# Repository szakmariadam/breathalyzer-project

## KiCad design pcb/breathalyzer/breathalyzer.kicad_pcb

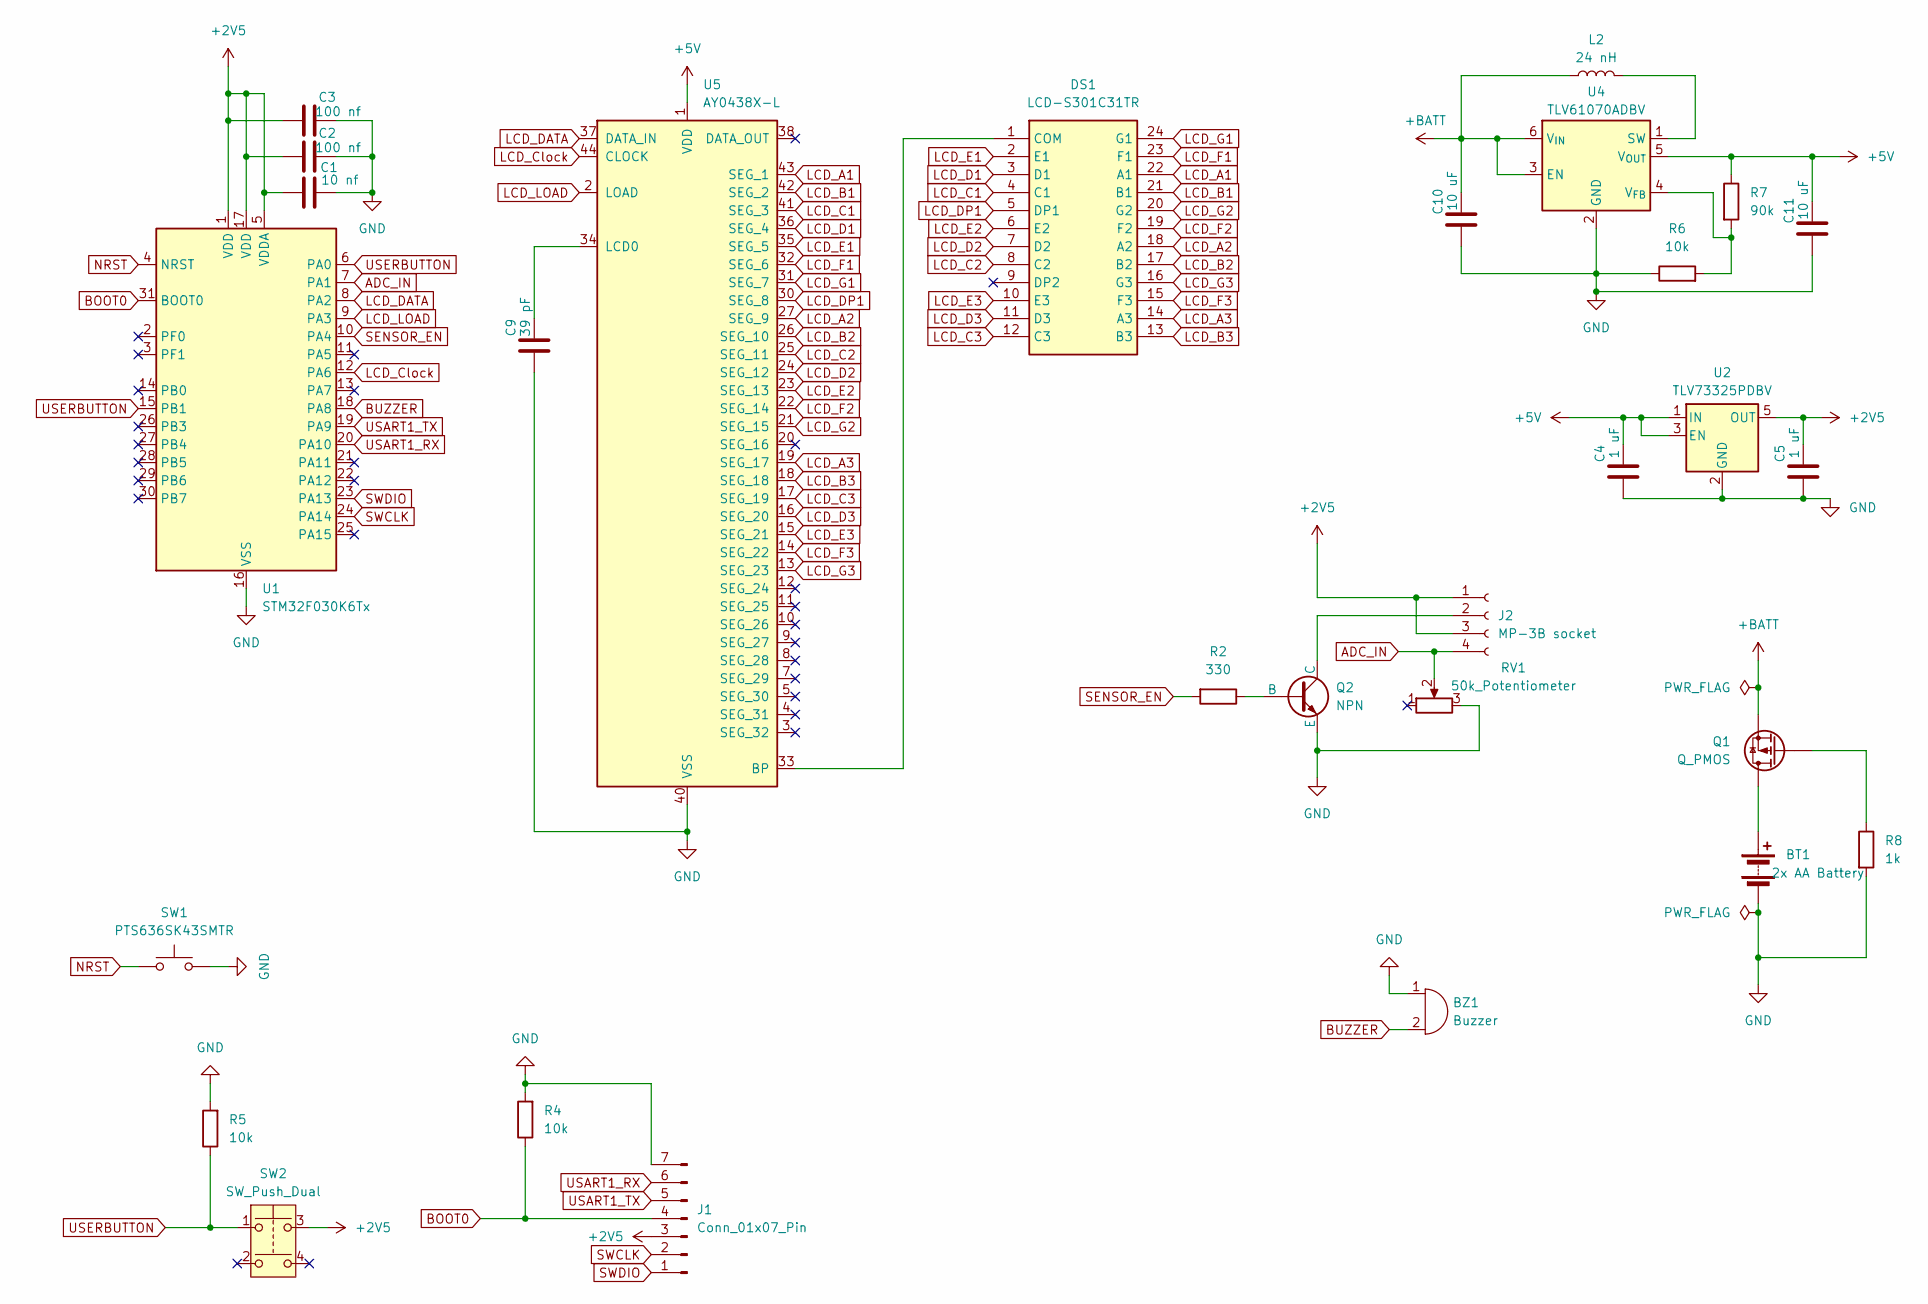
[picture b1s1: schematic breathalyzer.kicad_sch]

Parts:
BT1: 2x AA Battery; SHDRRA2W50P0X200_1X2_600X770X525P
BZ1: Buzzer; CPT1414680T
C1: 10 nf; C_01005_0402Metric
C2, C3: 100 nf; C_0402_1005Metric
C4, C5: 1 uF; C_0603_1608Metric
C9: 39 pF; C_0603_1608Metric
C10, C11: 10 uF; C_0805_2012Metric
DS1: LCD-S301C31TR; Mouser Part Number 696-LCD-S301C31TR
J1: Conn_01x07_Pin; HDRRA7W66P0X254_1X7_1778X229X274P
J2: MP-3B socket; 25SHB04TS
L2: 24 nH; L_1008_2520Metric
Q1: Q_PMOS; SOT-23-3
Q2: NPN; SOT-23-3
R2: 330; R_0805_2012Metric
R4, R5, R6: 10k; R_0603_1608Metric
R7: 90k; R_1206_3216Metric
R8: 1k; R_0603_1608Metric
RV1: 50k_Potentiometer; Potentiometer_ACP_CA9-H5_Horizontal
SW1: PTS636SK43SMTR; PTS636SM43JSMTRLFS
SW2: SW_Push_Dual; 430162085826
U1: STM32F030K6Tx; LQFP-32_7x7mm_P0.8mm
U2: TLV73325PDBV; SOT-23-5
U4: TLV61070ADBV; SOT-23-6
U5: AY0438X-L; PLCC-44

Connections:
+2V5: C1.1, C2.1, C3.1, C5.2, J1.3, J2.1, J2.3, SW2.3, U1.1 (VDD), U1.5 (VDDA), U1.17 (VDD), U2.5 (OUT)
+5V: C4.2, C11.2, R7.1, U2.1 (IN), U2.3 (EN), U4.5 (V_{OUT}), U5.1 (VDD)
+BATT: C10.2, L2.1, Q1.2 (S), U4.3 (EN), U4.6 (V_{IN})
ADC_IN: J2.4, RV1.2, U1.7 (PA1)
BOOT0: J1.4, R4.1, U1.31 (BOOT0)
BUZZER: BZ1.2 (-), U1.18 (PA8)
GND: BT1.2 (-), BZ1.1 (+), C1.2, C2.2, C3.2, C4.1, C5.1, C9.1, C10.1, C11.1, J1.7, Q2.3 (E), R4.2, R5.2, R6.1, R8.2, RV1.3, SW1.2, U1.16 (VSS), U1.32 (VSS), U2.2 (GND), U4.2 (GND), U5.40 (VSS)
LCD_A1: DS1.22 (A1), U5.43 (SEG_1)
LCD_A2: DS1.18 (A2), U5.27 (SEG_9)
LCD_A3: DS1.14 (A3), U5.19 (SEG_17)
LCD_B1: DS1.21 (B1), U5.42 (SEG_2)
LCD_B2: DS1.17 (B2), U5.26 (SEG_10)
LCD_B3: DS1.13 (B3), U5.18 (SEG_18)
LCD_C1: DS1.4 (C1), U5.41 (SEG_3)
LCD_C2: DS1.8 (C2), U5.25 (SEG_11)
LCD_C3: DS1.12 (C3), U5.17 (SEG_19)
LCD_Clock: U1.12 (PA6), U5.44 (CLOCK)
LCD_D1: DS1.3 (D1), U5.36 (SEG_4)
LCD_D2: DS1.7 (D2), U5.24 (SEG_12)
LCD_D3: DS1.11 (D3), U5.16 (SEG_20)
LCD_DATA: U1.8 (PA2), U5.37 (DATA_IN)
LCD_DP1: DS1.5 (DP1), U5.30 (SEG_8)
LCD_E1: DS1.2 (E1), U5.35 (SEG_5)
LCD_E2: DS1.6 (E2), U5.23 (SEG_13)
LCD_E3: DS1.10 (E3), U5.15 (SEG_21)
LCD_F1: DS1.23 (F1), U5.32 (SEG_6)
LCD_F2: DS1.19 (F2), U5.22 (SEG_14)
LCD_F3: DS1.15 (F3), U5.14 (SEG_22)
LCD_G1: DS1.24 (G1), U5.31 (SEG_7)
LCD_G2: DS1.20 (G2), U5.21 (SEG_15)
LCD_G3: DS1.16 (G3), U5.13 (SEG_23)
LCD_LOAD: U1.9 (PA3), U5.2 (LOAD)
NRST: SW1.1, U1.4 (NRST)
unnamed: BT1.1 (+), Q1.3 (D)
unnamed: DS1.1 (COM), U5.33 (BP)
unnamed: J2.2, Q2.1 (C)
unnamed: Q1.1 (G), R8.1
unnamed: Q2.2 (B), R2.1
unnamed: L2.2, U4.1 (SW)
unnamed: R6.2, R7.2, U4.4 (V_{FB})
unnamed: C9.2, U5.34 (LCD0)
SENSOR_EN: R2.2, U1.10 (PA4)
SWCLK: J1.2, U1.24 (PA14)
SWDIO: J1.1, U1.23 (PA13)
USART1_RX: J1.6, U1.20 (PA10)
USART1_TX: J1.5, U1.19 (PA9)
USERBUTTON: R5.1, SW2.1, U1.6 (PA0), U1.15 (PB1)

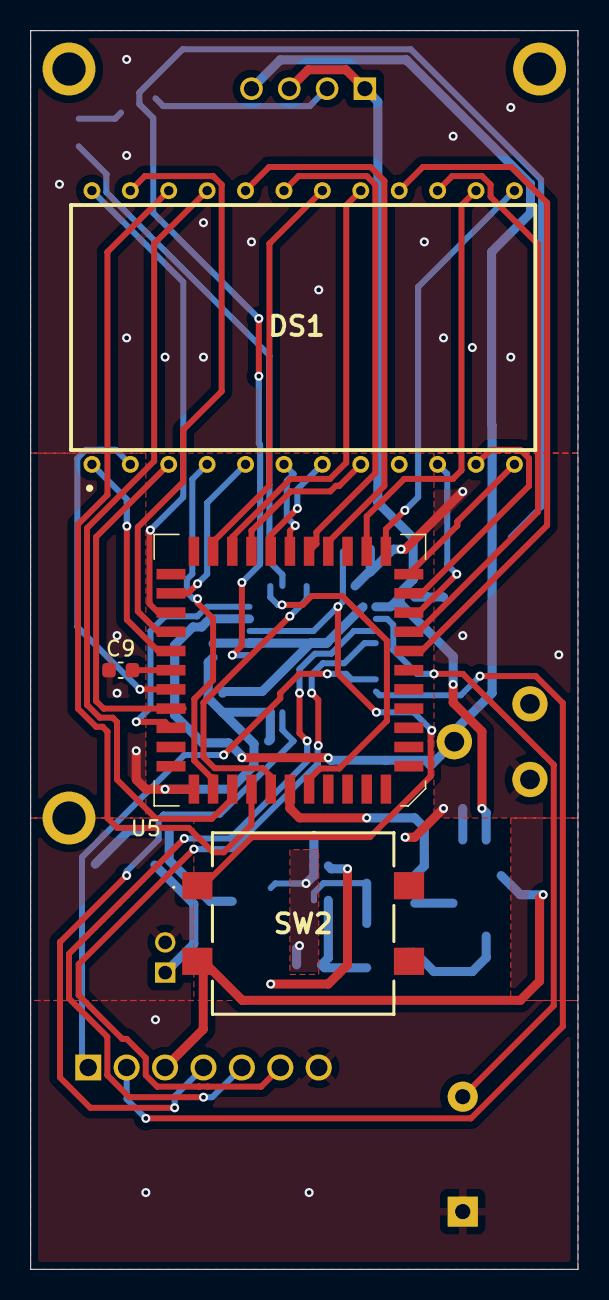
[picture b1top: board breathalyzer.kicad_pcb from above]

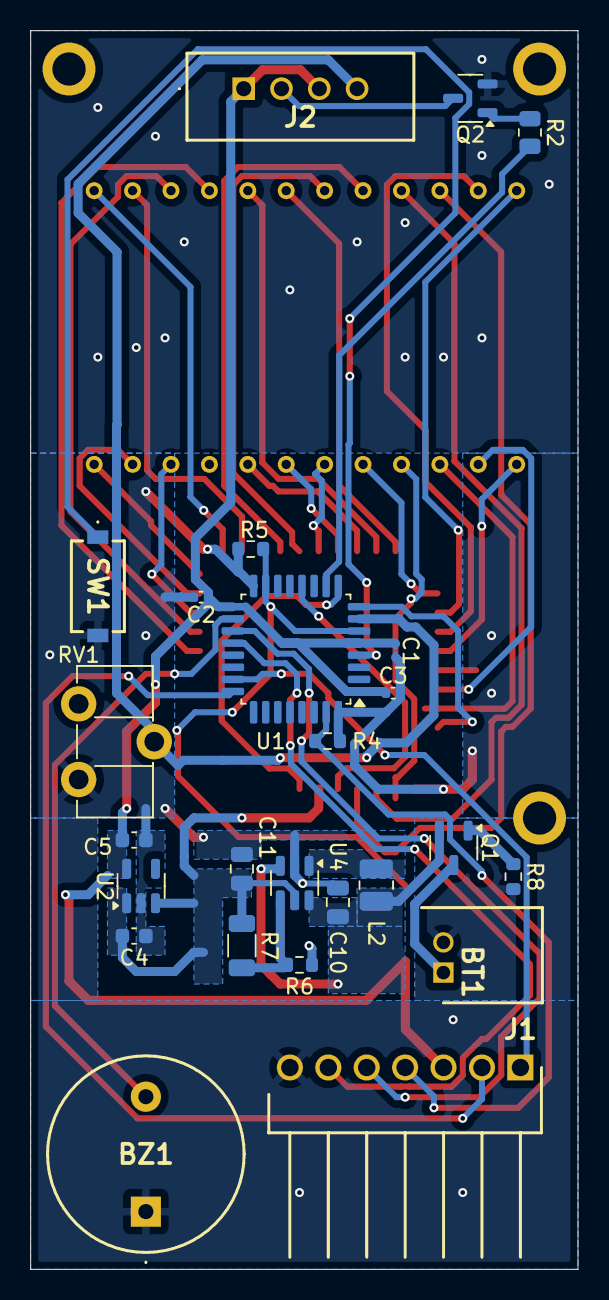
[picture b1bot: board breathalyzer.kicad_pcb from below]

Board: 2 copper layers, 36.2 x 81.9 mm, 32 parts (25 on the bottom side), 47 nets.

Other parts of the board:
H1, H1#2, H1#3: MountingHole; MountingHole_2.2mm_M2_ISO7380_Pad

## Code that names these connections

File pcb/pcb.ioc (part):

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Mcu.Name=STM32F030K6Tx
Mcu.Package=LQFP32
Mcu.UserName=STM32F030K6Tx
PA0.Mode=SYS_WakeUp0
PA0.Signal=SYS_WKUP1
PA1.Mode=IN1
PA1.Signal=ADC_IN1
PA10.Mode=Asynchronous
PA10.Signal=USART1_RX
PA13.Mode=Serial_Wire
PA13.Signal=SYS_SWDIO
PA14.Mode=Serial_Wire
PA14.Signal=SYS_SWCLK
PA2.Signal=GPIO_Output
PA3.Signal=GPIO_Output
PA4.GPIOParameters=PinState,GPIO_ModeDefaultOutputPP
PA4.GPIO_ModeDefaultOutputPP=GPIO_MODE_OUTPUT_PP
PA4.PinState=GPIO_PIN_RESET
PA4.Signal=GPIO_Output
PA6.Signal=S_TIM3_CH1
PA8.Signal=S_TIM1_CH1
PA9.Mode=Asynchronous
PA9.Signal=USART1_TX
PB1.Signal=GPXTI1
board=custom

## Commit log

2025-02-23 Empty project with LED blink
2025-02-23 GPIO8 for testing
2025-03-15 init GPIOs for 7 segment driver
2025-03-15 7 segment driver GPIOs testing
2025-03-16 Init ADC1
2025-03-19 project update
2025-03-19 polling ADC
2025-03-20 ADC calib
2025-03-20 PWM init
    Added HAL_ADC_Stop()
2025-03-26 ADC result averages
2025-03-27 PWM set to 2V31
2025-03-29 PWM set to 2V475
2025-03-30 project converted to CMake
2025-03-30 Imported project to vscode
2025-03-30 updated gitignore
2025-03-30 deleted ignored folders
2025-03-30 added back vscode config
2025-03-30 Enabled liveWatch in vscode
2025-03-30 setSegment function
2025-03-30 tim3 interrupt setup
    setSegment error handling
2025-03-31 Set up GPIOs to select digit
2025-04-02 7 segment driver
2025-04-02 7 segment driver fix
    display driver doesn't display empty digits
2025-04-02 set up user button
2025-04-02 ADC moved to PA1
    and sysWakeup was initialized on pa0
2025-04-03 callback function for TIM2
2025-04-03 10 sec timeout to standby
    init TIM4
    standby in interrupt
    wake up signal
2025-04-03 60 sec timeout to standby
2025-04-09 replaced blink with static power LED
    tim2 unused
2025-04-10 setup TIM2 as 1kHz 50D PWM for buzzer
    half sec beep on start
    commented standby timeout for dev
2025-04-14 UserButton GPIO changed
2025-04-14 added interrupt for UserButton
2025-04-15 removed the 1000 digit
    added fix decimal point
2025-04-15 7 segment displays 4.2f
2025-04-22 getADCvalue function
2025-04-22 sensor warmup function
2025-04-22 empty measure function on button press
2025-04-23 stop stby timeout while measuring
2025-04-23 moved measure function to TIM3 interrupt
    basic ADC measuring for 10 sec
    commented out timeout for dev
2025-04-23 calculated sensor resistance
2025-04-24 ADC ref voltage calibration
    RLVoltage for debug
2025-04-25 fixed buzzer
2025-04-25 adjusted getADCvalue() and measure time
2025-04-26 Calculate BAC% from sensor resistance
2025-05-04 empty kicad project
2025-05-06 LDO 2V5
2025-05-07 voltage reference
2025-05-08 boost 3v3
2025-05-08 program MCU
2025-05-08 Serial debug
2025-05-08 reset button
2025-05-09 change pull-down resistor for BOOT0 and bootloader mode
2025-05-09 wakeup button
2025-05-09 display parts chosen
2025-05-10 numeric LCD display and driver
    +5V boost
    previous parts scrapped
2025-05-10 removed 3V3 boost
2025-05-10 Userbutton
2025-05-10 buzzer
2025-05-11 reverse polarity protection
2025-05-11 changed power supply
    5V boost from BATT
    2V5 LDO from 5V
2025-05-19 sensor connector
2025-05-20 finalized schematic
2025-05-20 update from schematic
2025-05-20 test
    modified RL
    added round() to BAC
    fixed 10s heatup
2025-05-20 net classes
2025-05-20 5V fix
2025-05-20 +2V5
2025-05-22 pcb layout
2025-05-22 layout update
2025-05-22 layout update
    shorter board
2025-05-22 added 3d models
2025-05-23 all models
2025-05-23 traces
2025-05-23 trace correction
2025-05-23 layout correction
2025-05-23 unfilled GND zones
2025-05-23 GND zones with cutout power area
2025-05-23 pcb complete no errors
2025-05-23 extra vias
2025-05-23 mounting holes
2025-05-23 no warnings
2025-05-25 layout update
    C closer to MCU
2025-05-26 adjustments
2025-05-26 enable standby timeout
2025-05-30 documentation
2025-05-31 complete documentation docx
2025-05-31 documentation pdf
